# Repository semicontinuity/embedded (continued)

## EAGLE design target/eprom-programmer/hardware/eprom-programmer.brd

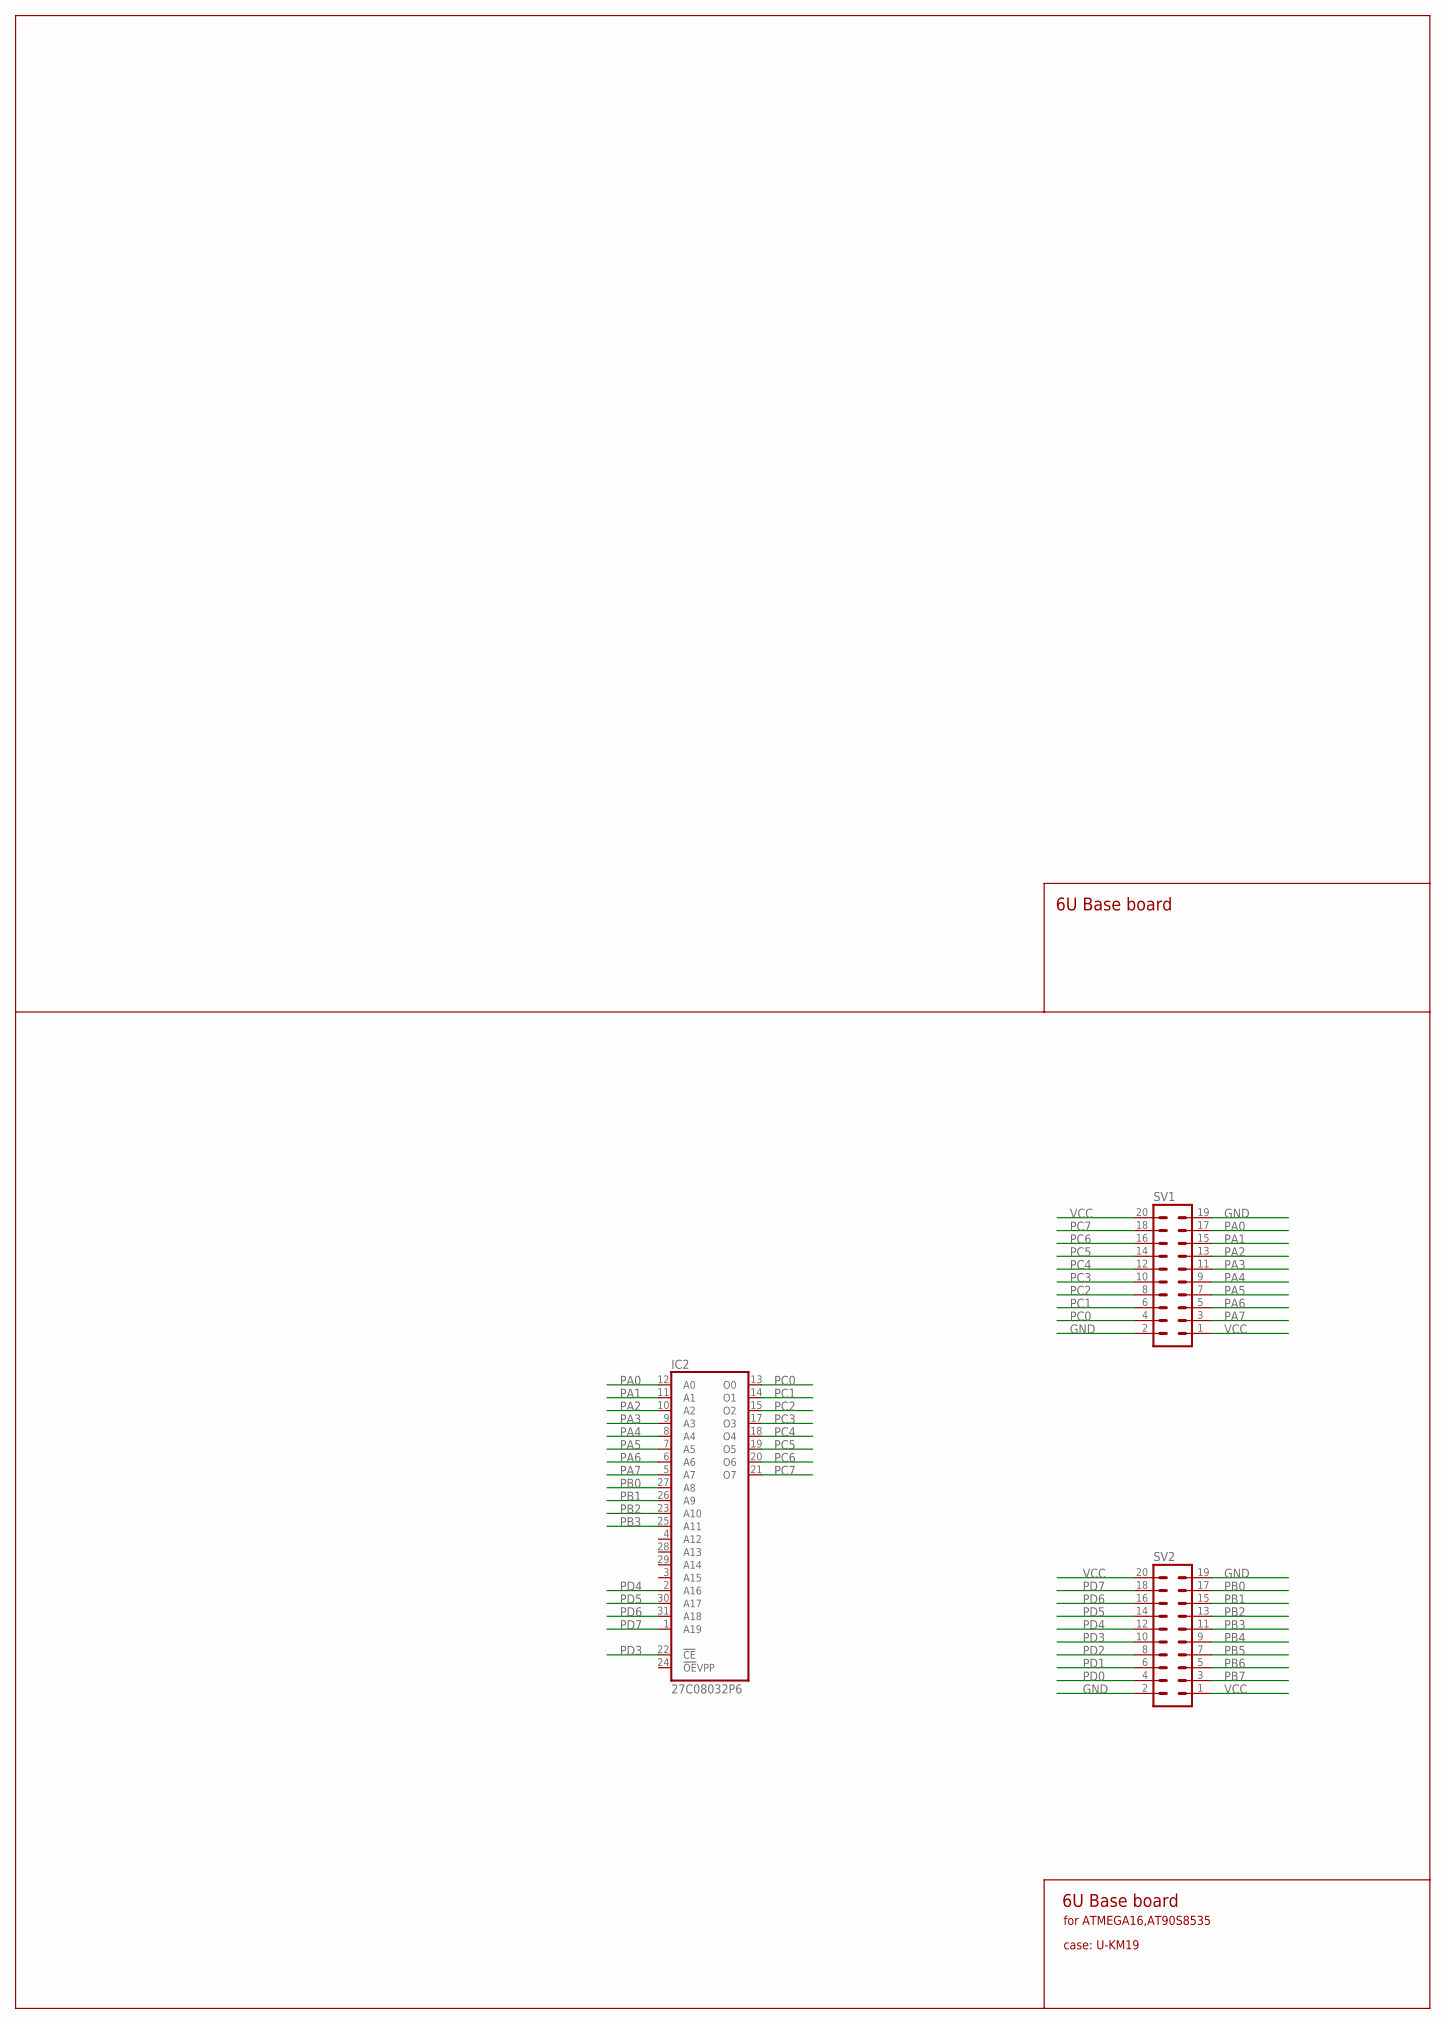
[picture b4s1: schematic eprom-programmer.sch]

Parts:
IC2: 27C08032P6; DIL32
SV1, SV2: MA10-2

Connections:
GND: IC2.16 (GND), SV1.2, SV1.19, SV2.2, SV2.19
PA0: IC2.12 (A0), SV1.17
PA1: IC2.11 (A1), SV1.15
PA2: IC2.10 (A2), SV1.13
PA3: IC2.9 (A3), SV1.11
PA4: IC2.8 (A4), SV1.9
PA5: IC2.7 (A5), SV1.7
PA6: IC2.6 (A6), SV1.5
PA7: IC2.5 (A7), SV1.3
PB0: IC2.27 (A8), SV2.17
PB1: IC2.26 (A9), SV2.15
PB2: IC2.23 (A10), SV2.13
PB3: IC2.25 (A11), SV2.11
PB4: SV2.9
PB5: SV2.7
PB6: SV2.5
PB7: SV2.3
PC0: IC2.13 (O0), SV1.4
PC1: IC2.14 (O1), SV1.6
PC2: IC2.15 (O2), SV1.8
PC3: IC2.17 (O3), SV1.10
PC4: IC2.18 (O4), SV1.12
PC5: IC2.19 (O5), SV1.14
PC6: IC2.20 (O6), SV1.16
PC7: IC2.21 (O7), SV1.18
PD0: SV2.4
PD1: SV2.6
PD2: SV2.8
PD3: IC2.22 (!CE), SV2.10
PD4: IC2.2 (A16), SV2.12
PD5: IC2.30 (A17), SV2.14
PD6: IC2.31 (A18), SV2.16
PD7: IC2.1 (A19), SV2.18
VCC: IC2.32 (VCC), SV1.1, SV1.20, SV2.1, SV2.20

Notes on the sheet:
6U Base board
for ATMEGA16,AT90S8535
case: U-KM19

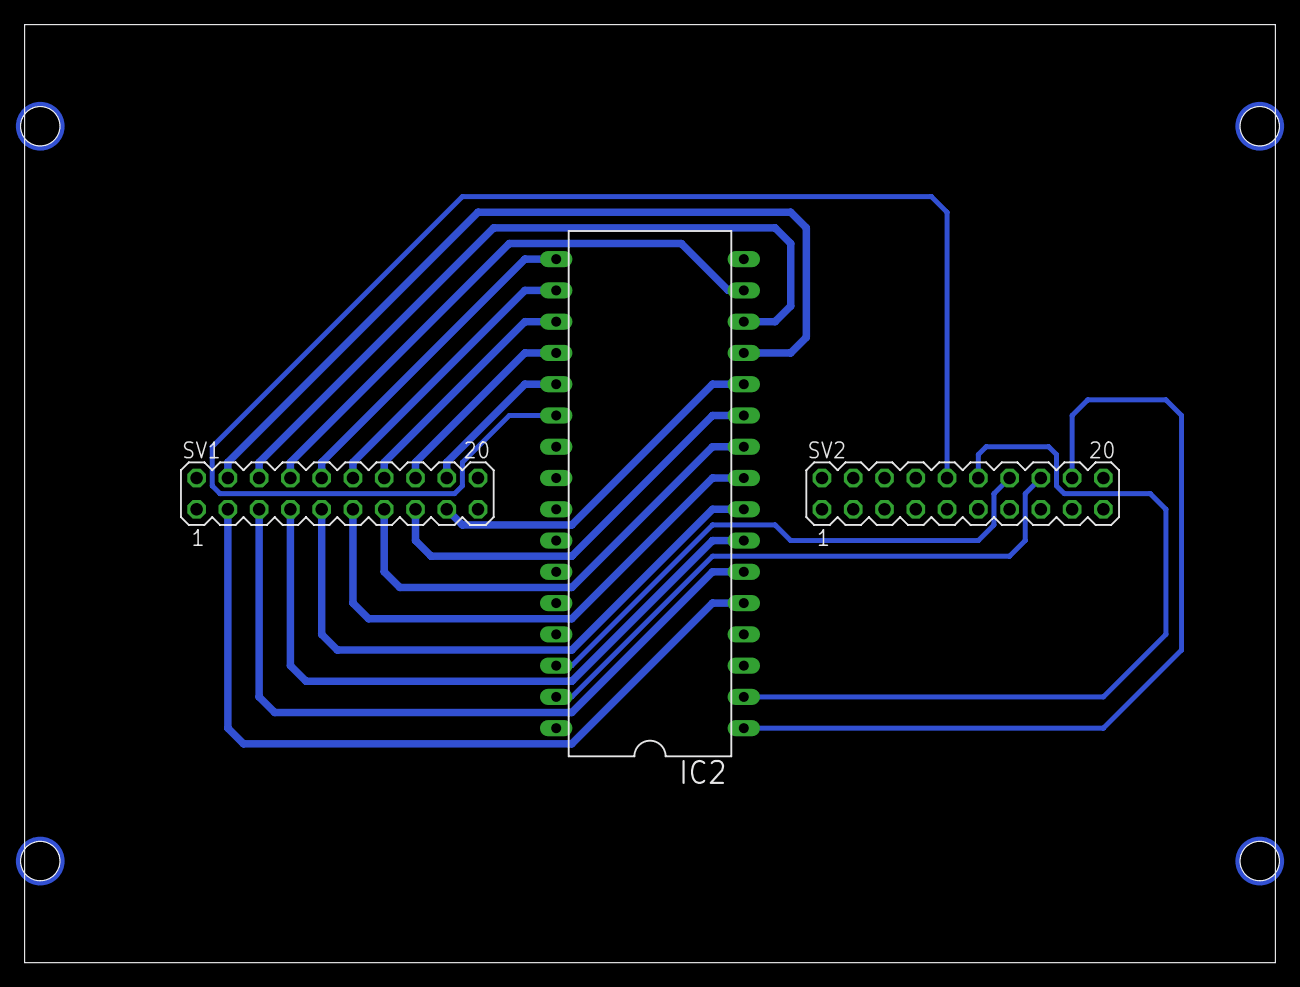
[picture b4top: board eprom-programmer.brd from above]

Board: 2 copper layers, 101.6 x 76.2 mm, 3 parts (0 on the bottom side), 27 nets.

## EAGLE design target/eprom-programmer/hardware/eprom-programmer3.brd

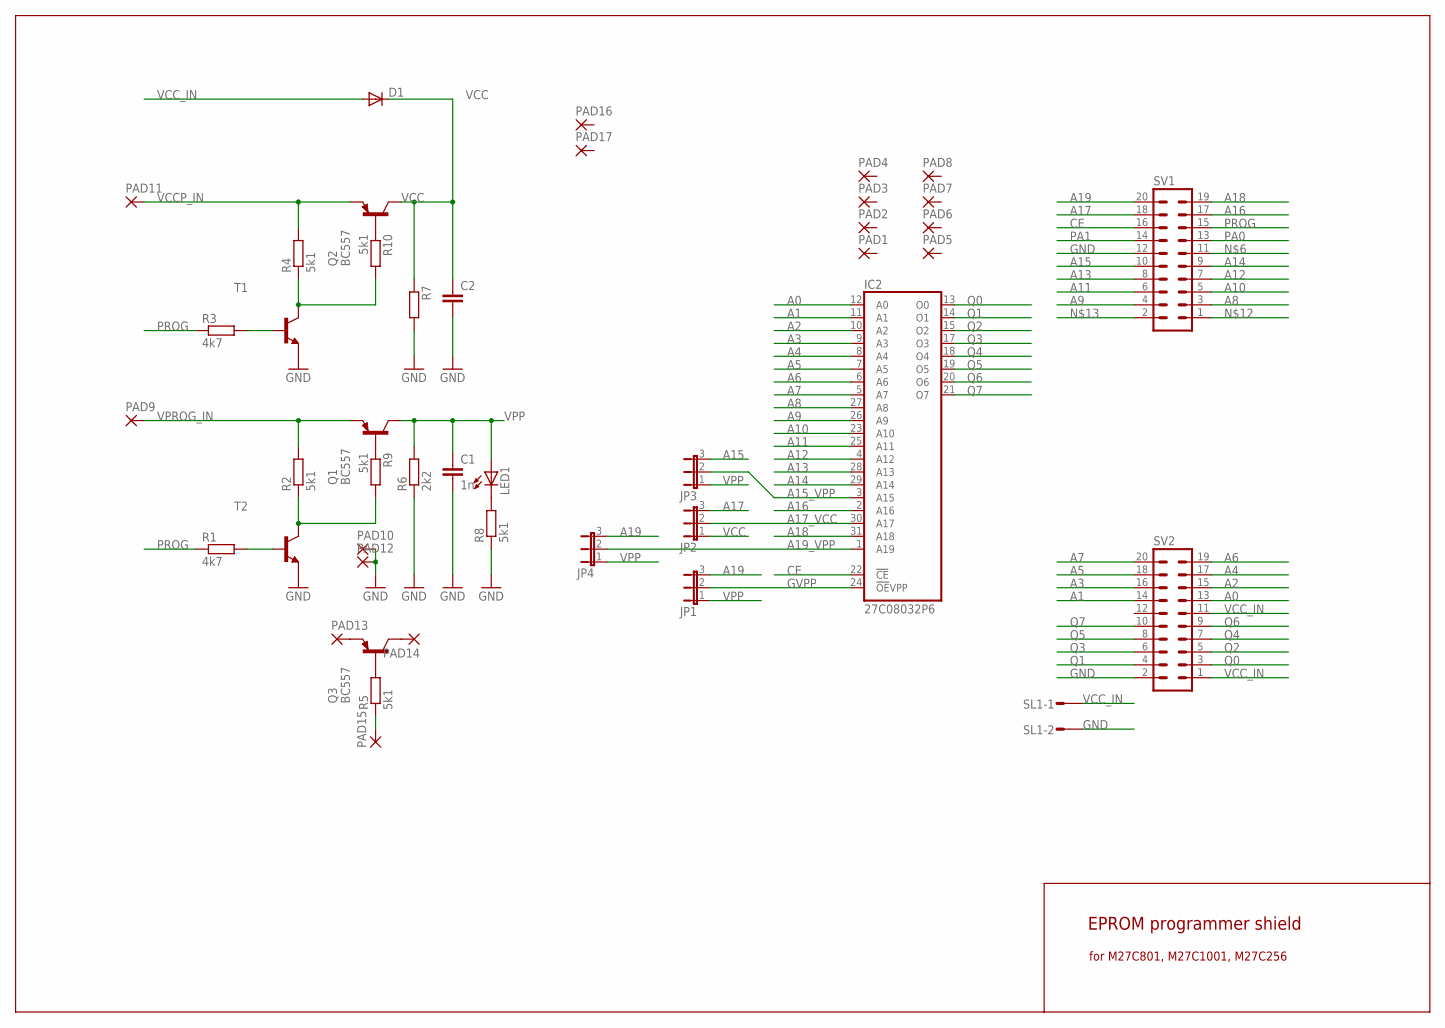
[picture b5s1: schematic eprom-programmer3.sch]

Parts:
C1: 1n; C025-024X044
C2: C-EUC0805; C0805
D1: DIODE-MINIMELF; MINIMELF
IC2: 27C08032P6; DIL32
JP1, JP2, JP3, JP4: JP2E; JP2
LED1: LED3MM
PAD1, PAD2, PAD3, PAD4, PAD5, PAD6, PAD7, PAD8, PAD9, PAD10, PAD11, PAD12, PAD13, PAD14, PAD15, PAD16, PAD17: 1,6/0,8
Q1, Q2, Q3: BC557; TO92-EBC
R1, R3: 4k7; 0207/2V
R2, R4, R5, R8: 5k1; 0207/2V
R6: 2k2; 0207/2V
R7: R-EU_M0805; M0805
R9, R10: 5k1; M0805
SL1: MA02S; 02PA
SV1, SV2: MA10-2
T1, T2: BC547-NPN-TO92-CBE; TO92-CBE

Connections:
A0: IC2.12 (A0), SV2.13
A1: IC2.11 (A1), SV2.14
A2: IC2.10 (A2), SV2.15
A3: IC2.9 (A3), SV2.16
A4: IC2.8 (A4), SV2.17
A5: IC2.7 (A5), SV2.18
A6: IC2.6 (A6), SV2.19
A7: IC2.5 (A7), SV2.20
A8: IC2.27 (A8), SV1.3
A9: IC2.26 (A9), SV1.4
A10: IC2.23 (A10), SV1.5
A11: IC2.25 (A11), SV1.6
A12: IC2.4 (A12), SV1.7
A13: IC2.28 (A13), SV1.8
A14: IC2.29 (A14), SV1.9
A15: JP3.3, SV1.10
A15_VPP: IC2.3 (A15), JP3.2
A16: IC2.2 (A16), SV1.17
A17: JP2.3, SV1.18
A17_VCC: IC2.30 (A17), JP2.2
A18: IC2.31 (A18), SV1.19
A19: JP1.3, JP4.3, SV1.20
A19_VPP: IC2.1 (A19), JP4.2
CE: IC2.22 (!CE), SV1.16
GND: C1.2, C2.2, IC2.16 (GND), PAD10.1, PAD12.1, R6.1, R7.2, R8.1, SL1.2, SV1.12, SV2.2, T1.E, T2.E
GVPP: IC2.24 (!OE!VPP), JP1.2
unnamed: R3.2, T1.B
unnamed: R4.1, R10.2, T1.C
unnamed: R1.2, T2.B
unnamed: R2.1, R9.2, T2.C
unnamed: Q3.B, R5.2
unnamed: PAD13.1, Q3.E
unnamed: PAD14.1, Q3.C
unnamed: PAD15.1, R5.1
unnamed: LED1.K (C), R8.2
unnamed: Q1.B, R9.1
unnamed: Q2.B, R10.1
PA0: SV1.13
PA1: SV1.14
PROG: R1.1, R3.1, SV1.15
Q0: IC2.13 (O0), SV2.3
Q1: IC2.14 (O1), SV2.4
Q2: IC2.15 (O2), SV2.5
Q3: IC2.17 (O3), SV2.6
Q4: IC2.18 (O4), SV2.7
Q5: IC2.19 (O5), SV2.8
Q6: IC2.20 (O6), SV2.9
Q7: IC2.21 (O7), SV2.10
VCC: C2.1, D1.C, IC2.32 (VCC), JP2.1, Q2.C, R7.1
VCCP_IN: PAD11.1, Q2.E, R4.2
VCC_IN: D1.A, SL1.1, SV2.1, SV2.11
VPP: C1.1, JP1.1, JP3.1, JP4.1, LED1.A, Q1.C, R6.2
VPROG_IN: PAD9.1, Q1.E, R2.2

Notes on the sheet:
EPROM programmer shield
for M27C801, M27C1001, M27C256

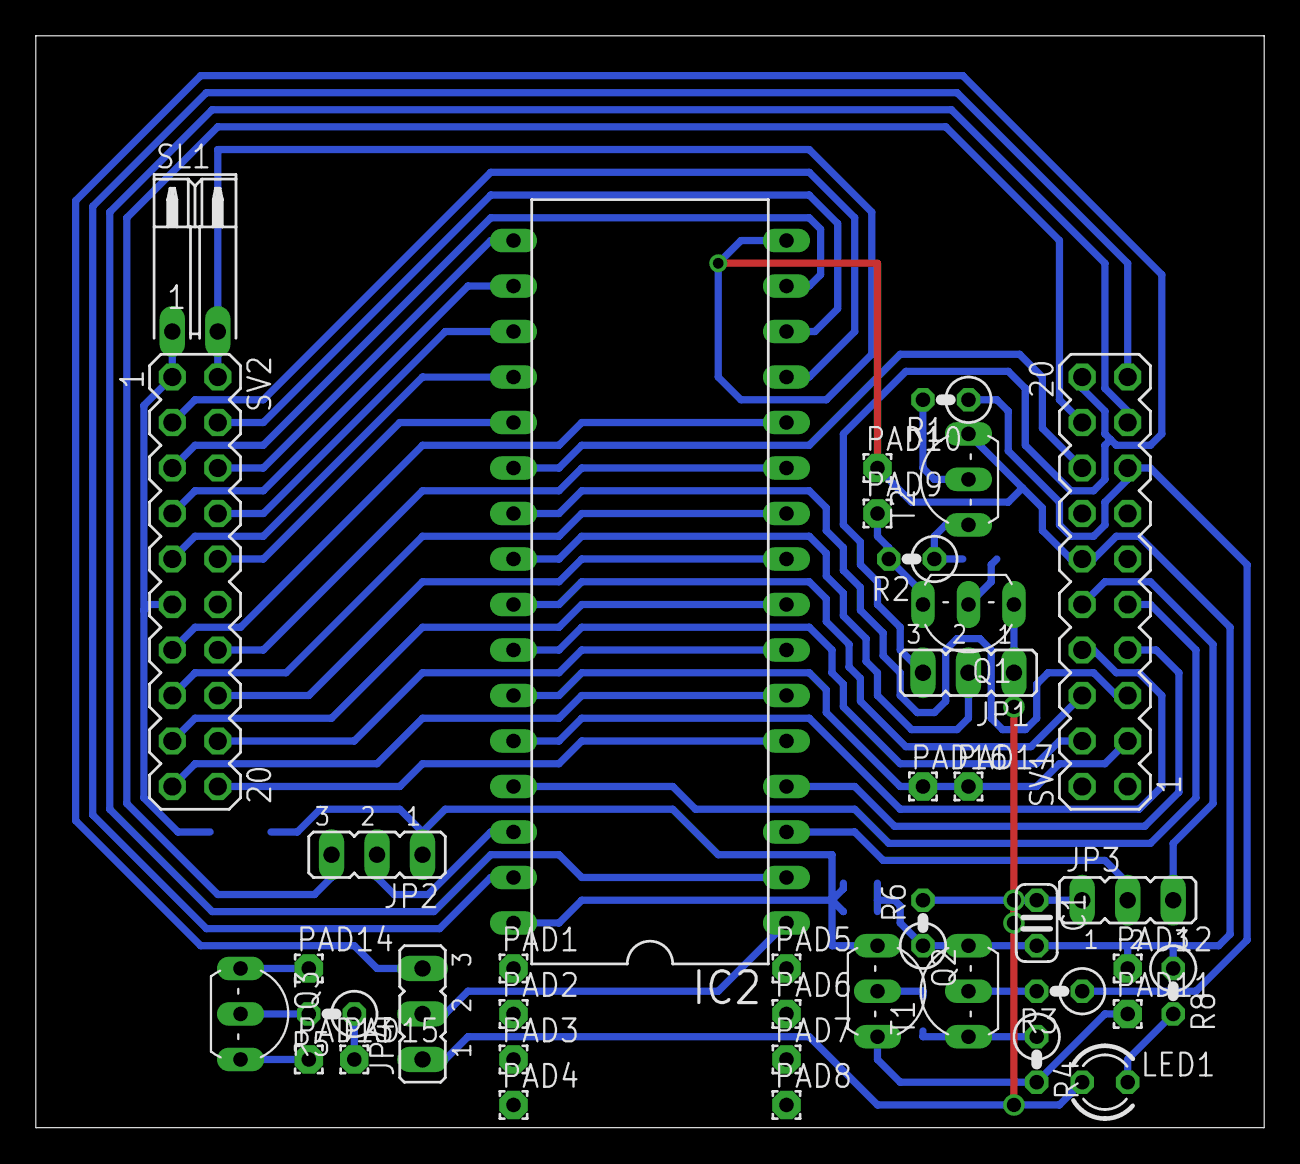
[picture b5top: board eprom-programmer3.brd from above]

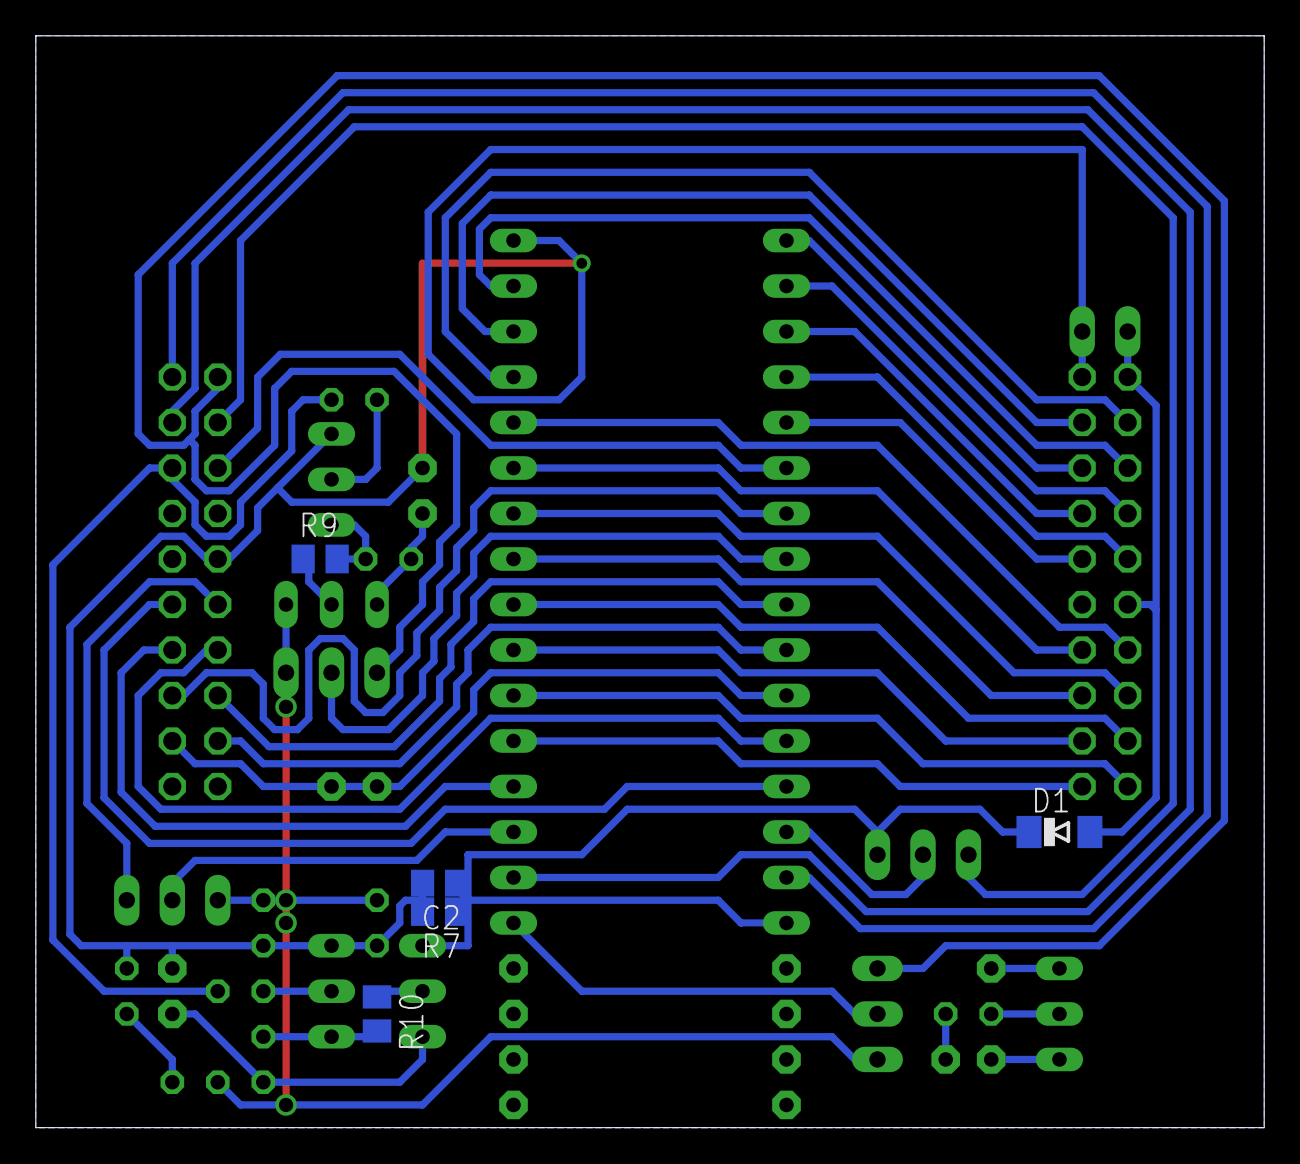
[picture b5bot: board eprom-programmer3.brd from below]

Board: 2 copper layers, 68.6 x 61.0 mm, 44 parts (5 on the bottom side), 51 nets.
